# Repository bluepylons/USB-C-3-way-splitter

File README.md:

# A USB-C 3-way-splitter for charging multiple 5W devices from a single USB-PD charger

*Disclaimer* - **Build and/or use this at your own  risk. I am not responsible for anything that arises from use of these files or documents, or for anything that arises from constructing and/or using this device.**

*Disclaimer 2* - the USB battery charging standard actually provides [for a maximum of 1.5A](https://imgur.com/07zPKKw), not 1A as originally believed. The polyfuse used (Littelfuse 1812L300MR) does not reliably trip below 5A, so this splitter may result in 4.5A maximum being drawn from the source. A planned Version 4 (which uses an 3A electronic fuse in place of the high-side switch to reliabily cut off current at around 3A) is being developed to address this issue. UPDATE August 19, 2024 - Version 4 does not work as the ENABLE pin logic for the electronic fuse was inverted. Version 5 is planned to fix this. 

This is a USB-C splitter that splits a 5V 3A-capable USB-C power source to 3 5V 1A  sources. This is for using a single-port USB-C PD charger to charge multiple 5V USB-C devices at once. Files are done in KiCAD 8, and manufacturing files for JLCPCB are provided. An enclosure design is included (which was designed in Autodesk Fusion 360) - .3mf, .step, and .f3z file are provided. 

This design has been prototyped and  tested. 

## Background
With the widespread adoption of USB-C for device charging, I can now travel with a single compact 45W USB-C GaN charger and cable, and charge all my USB-C devices (phone, laptop, camera, flashlight, power bank, headphones, etc.) with that one charger. However, having a single cable and single charger is often limiting when I need to charge multiple devices, especially overnight, and many USB-C devices only need 5V and not many watts for overnight charging. This splitter goes onto an existing USB-C cable, for charging those devices simultaneously with a single charger, without needing a bulkier multi-port charger and multiple cables. 

## Operation 
For safety, the splitter outputs only power on when the splitter is connected to a charger that indicates it can actually supply 3A, and includes a resettable fuse for overcurrent protection. The white LED lights up when it is connected to a powered USB-C cable. The green LED lights up if the power source is capable of supplying 5V 3A, and indicates the outputs have been powered on.

The outputs have D+ and D- shorted to indicate that they can supply ~~~1A~~~ 1.5A of current (per the USB Battery Charging standard). 

## Design
The splitter only powers on with USB-C inputs capable of supplying 5V 3A. This is done by monitoring the USB-C CC lines and checking that the signal there is greater than 1.25V. Under the USB-PD standard, if the voltage on the CC pin [is greater than 1.31V](https://hackaday.com/2023/01/04/all-about-usb-c-resistors-and-emarkers/), it indicates the source is capable of supplying 5V 3A. Only then are the outputs powered on (as indicated by the green LED). Otherwise, the outputs are turned off. 

The CC line voltage checking is done by a pair of comparators that monitor each of the 2 CC lines (as the USB-C input cable can be plugged in either way). The CC line voltage are compared against a 1.25V reference voltage (provided by an ST TS4061AICT-1.25 shunt diode reference) - a 1.31V voltage reference would have been more precise, but were not easily available, and 1.25V is above the 1.16V cutoff for a 1.5A source and works fine. The output of the comparators are fed through a pair of diodes (functioning as an OR gate) to the ENABLE input on an SiP32509 high-side switch that turns the outputs on and off. The device is over-current protected by a 3A resettable fuse (Littelfuse 1812L300MR). The CC lines and +5V bus are ESD protected with an SRV05-4 ESD diode array and an ESD5Z5V0 TVS diode.

Note that the output cables need 56K pull-up resistors between output CC and 5V to comply with the USB-C protocol - some devices may not charge if these resistors are missing. USB-A to USB-C cables are required to include this resistor, so using the USB-C end from a cut-up USB-A to C cable is recommended for the output cables. 

A 3D-printed enclosure design is supplied in the Enclosure folder. The enclosure design is meant to be 3D-printed in two halves; on mine these were printed with translucent PETG to allow the indicator LEDs to shine through. The lower enclosure features embedded M3 nuts - **the print must be paused at the appropriate layer and M3 nuts need to be inserted before the print resumes**. The two halves are screwed together with M3x8 countersunk screws. The enclosure is designed to use [Ikea  SITTBRUNN](https://www.ikea.com/us/en/p/sittbrunn-usb-a-to-usb-c-light-yellow-80539483/) USB-A to USB-C cables, as these are widely available and inexpensive. The ends are wrapped in Qualtek Q5-3X-3/16-01-QB48IN-25 adhesive heatshrink for strain relief. To dissipate heat from the SiP32509 high-side switch (U2), which is expected to generate about 0.4W of heat at 3A, either the enclosure must be potted to facilitate heat transfer, or a thermal pad must be used between the SiP32509 and the case. [Lower-enclosure-potted](https://github.com/bluepylons/USB-C-3-way-splitter/blob/main/Enclosure/Lower-enclosure-potted.3mf) has a small hole to inject potting compound (or hot glue, or silicone) into the case - use a high viscosity potting compound to avoid it getting in the input USB-C connector. [Lower-enclosure-thermal-pad](https://github.com/bluepylons/USB-C-3-way-splitter/blob/main/Enclosure/Lower-enclosure-thermal-pad.3mf) has a small raised feature above the SiP32509 IC to place a 1.5mm thick thermal pad between it and the case. 

# ORDERING GUIDE

## Bill Of Materials

### Custom Parts
| Description                                                                                                                                                                                                                                           | Quantity  | Notes | 
| ----------------------------------------------------------------------------------------------------------------------------------------------------------------------------------------------------------------------------------------------------- | --------- | - |
| [PCB](https://github.com/bluepylons/USB-C-3-way-splitter/tree/main/Manufacturing%20files)                                                                                                                                                             | 1         | See "Ordering the PCB" section below  | 
| [Upper enclosure](https://github.com/bluepylons/USB-C-3-way-splitter/blob/main/Enclosure/Upper-enclosure.3mf)                                                                                                                                         | 1         | FDM 3D-printed  |
| Lower enclosure ([thermal pad](https://github.com/bluepylons/USB-C-3-way-splitter/blob/main/Enclosure/Lower-enclosure-thermal-pad.3mf) or [potted](https://github.com/bluepylons/USB-C-3-way-splitter/blob/main/Enclosure/Lower-enclosure-potted.3mf)) | 1         | FDM 3D-printed. Has 4 embedded M3 nuts, which must be installed while 3D printing | 

The 3D-printed parts were FDM 3D-printed in PETG, though other materials probably work fine here. A translucent or semi-translucent material is recommended so that the indicator LEDs can shine through. 

## Off-the-shelf parts

| Description                                                                                                         | Part number                              | Quantity | Notes                                         | 
| ------------------------------------------------------------------------------------------------------------------- | ---------------------------------------- | -------- | --------------------------------------------- |
| [Ikea Sittbrunn USB-A to USB-C cable](https://www.ikea.com/us/en/p/sittbrunn-usb-a-to-usb-c-light-yellow-80539483/) | Ikea 805.394.83                          | 3        |                                               | 
| M3 hex nut, DIN 934, zinc-plated steel                                                                              | McMaster-Carr 90591A250                  | 4        | Generic. Not stainless steel to avoid galling |
| M3x8 flat head screw, DIN 7991 / ISO 10642, hex drive, 18-8 stainless steel                                         | McMaster-Carr 92125A128                  | 4        | Generic                                       |
| Adhesive-lined heat-shrink, 3/16" / 4.8mm ID, 3:1 shrink ratio                                                      | Qualtek Qualtek Q5-3X-3/16-01-QB48IN-25  | 3x 25mm  |                                               |

If you are using the [thermal pad option](https://github.com/bluepylons/USB-C-3-way-splitter/blob/main/Enclosure/Lower-enclosure-thermal-pad.3mf) for the lower enclosure, you will need 1.5mm thick thermal pads. I used Thermalright Extreme Odyssey 1.5mm pads for the ones I have built, but other 1.5mm thermal pads (e.g. Arctic TP-3) may work. The thermal pad must not be electrically conductive. 

If you are using the [potted option](https://github.com/bluepylons/USB-C-3-way-splitter/blob/main/Enclosure/Lower-enclosure-potted.3mf) for the lower enclosure, you will need some sort of potting compound that can be injected through a 5mm diameter hole. The ones I built used hot glue. Make sure the potting compound has high enough viscosity to not get into the input USB-C port. 

## Ordering the PCB

The PCB can be ordered from [JLCPCB](https://jlcpcb.com/) in China, and the files are provided in their format. 

1.)  Go to JLCPCB, and press "Order Now". 

2.) Next, you want to upload the [Gerber ZIP file](https://github.com/bluepylons/USB-C-3-way-splitter/blob/main/PCB%20manufacturing%20files/V3%20Gerbers.zip) for the PCB. 

3.) Specify the following options once the Gerber file has uploaded. Non-default settings are highlighted in red. 

For color, specify a color supported by JLCPCB's ["Economic PCB Assembly"](https://jlcpcb.com/capabilities/pcb-assembly-capabilities). As of June 30, 2024, green, black, blue, red, white, and purple are supported. Note that some colors might incur an extra fee.

4.) Under "PCB Assembly", specify the following options:

5.) Press "Next":

6.) Upload the [BOM](https://github.com/bluepylons/USB-C-3-way-splitter/blob/main/PCB%20manufacturing%20files/JLCPCB-BOM.xls) and [CPL](https://github.com/bluepylons/USB-C-3-way-splitter/blob/main/PCB%20manufacturing%20files/JLCPCB-CPL.xls) files:

7.) Confirm  the components in the next page. If any components are listed as "Shortfall", JLCPCB does not have enough of them in stock and will not install them on any PCBs. You will have to purchase them from and solder them on yourself. Alternatively, you can wait for JLCPCB to restock the part.

8.) Next is the component placement confirmation page. You should not have to change anything here:

9.) You will need to describe the item in the next page for customs purposes. As of June 30th, 2024, I could not find an option most suitable for this, so select "Office Appliances and Accessories > Others" in the options, and type in "USB cable splitter PCB".

# BUILD GUIDE

## Tools needed 
| Tool           | Purpose                                                                                                                                                     |
| -------------- | ----------------------------------------------------------------------------------------------------------------------------------------------------------- | 
| Flush cutters  | Stripping wires, trimming leads                                                                                                                             |
| Soldering iron | Soldering the USB-C output cables to the PCB                                                                                                                |
| Solder         | You need it to solder                                                                                                                                       |
| Flux           | Makes tinning the output cables easier                                                                                                                      |
| Heat gun       | For the heat-shrink strain relief                                                                                                                           |
| Wire strippers | For stripping wire                                                                                                                                          |

If you are using the thermal pad option for the lower case, you will need scissors to cut the thermal pad. If you are using the potted option, you will need potting compound and whatever tools needed to inject into the hole in the case.

## Build process 

1.) Test the PCB by plugging in a 5V 3A-capable USB-C source. When plugged in, both the white and green LEDs should light up. Next, test it with a non-5V 3A capable source (e.g. use a USB-A cable). When plugged in, only the white LED should light up. 

2.) Unplug the PCB. 

3.) Take the Ikea Sittbrunn USB-A to USB-C cable, and cut the USB-C end to about 20-30mm longer than the desired length.

4.) Strip about 20mm off the outer insulation. The method I found works well is to use a pair of flush cutters to "bite' the insulation parallel to the cable, and then cut the resulting pieces off. After stripping, check that the insulation for the individual wires are not damaged. 

5.) Strip about 10mm off the inner insulation for one of the wires.

6.) Wind  the strands tightly with your hands. 

7.) Apply some flux to the stripped wire.

8.) Tin the wire with a little bit of solder. Try to add enough solder here that the strands don't come apart, but not so much that the stranded wires no longer fit in the output footprint through-holes in the PCB. 

9.) Repeat Steps 5 through 8 for the remaining wires. This is best done one wire at a time to prevent the wires from becoming unstranded from bumping into each other. 

10.) Cut some pieces of heat-shrink that are 20-30mm long:

11.) Put the heat shrink through the cable.

12.) Solder the wires to one of the three output footprints, and trim off any excess using the flush cutters.

The following wire colors correspond to the following pins, which are labelled on the underside of the PCB:

| Color | Pin |
| ----- | --- |
| Black | GND |
| Green | D-  |
| White | D+  |
| Red   | +5V |

Check that the strands from each wire are not shorted to each other. However, since D+ and D- are shorted to each other on the PCB per the USB Battery Charging standard, it does not matter if those two specific wires are shorted to each other. 

13.) Repeat steps 3-12 for the remaining outputs. **Remember to slip the heatshrink tubing on before soldering**. Double check that wires are not shorted to each other. 

14.) Plug the PCB into the 5V 3A USB-C source again. Check that the green and the white lights both light up. If not, you may have a short circuit somewhere.

15.) Move the heatshrink tubing down the cables, like so:

17.) Using a heatgun, shrink the heatshrink:

18.) (For the thermal pad variant only) - Cut a piece of thermal pad to about the size and shape of the raised portion marked in red, and place it on there:

19.) Place the PCB and the soldered wires onto the lower enclosure like so:

20.) Place the upper enclosure on, and attach it with the 4 M3x8 flat head screws.

21.) Test the splitter by plugging it into the 5V 3A source again, and using it to charge various devices (e.g. a phone). Make sure each output works. If not, check your soldering. 

22.) (For the potted variant only) - Inject potting compound into the 5mm hole on the lower enclosure, and it let it dry/solidify/cure. 

You are done!

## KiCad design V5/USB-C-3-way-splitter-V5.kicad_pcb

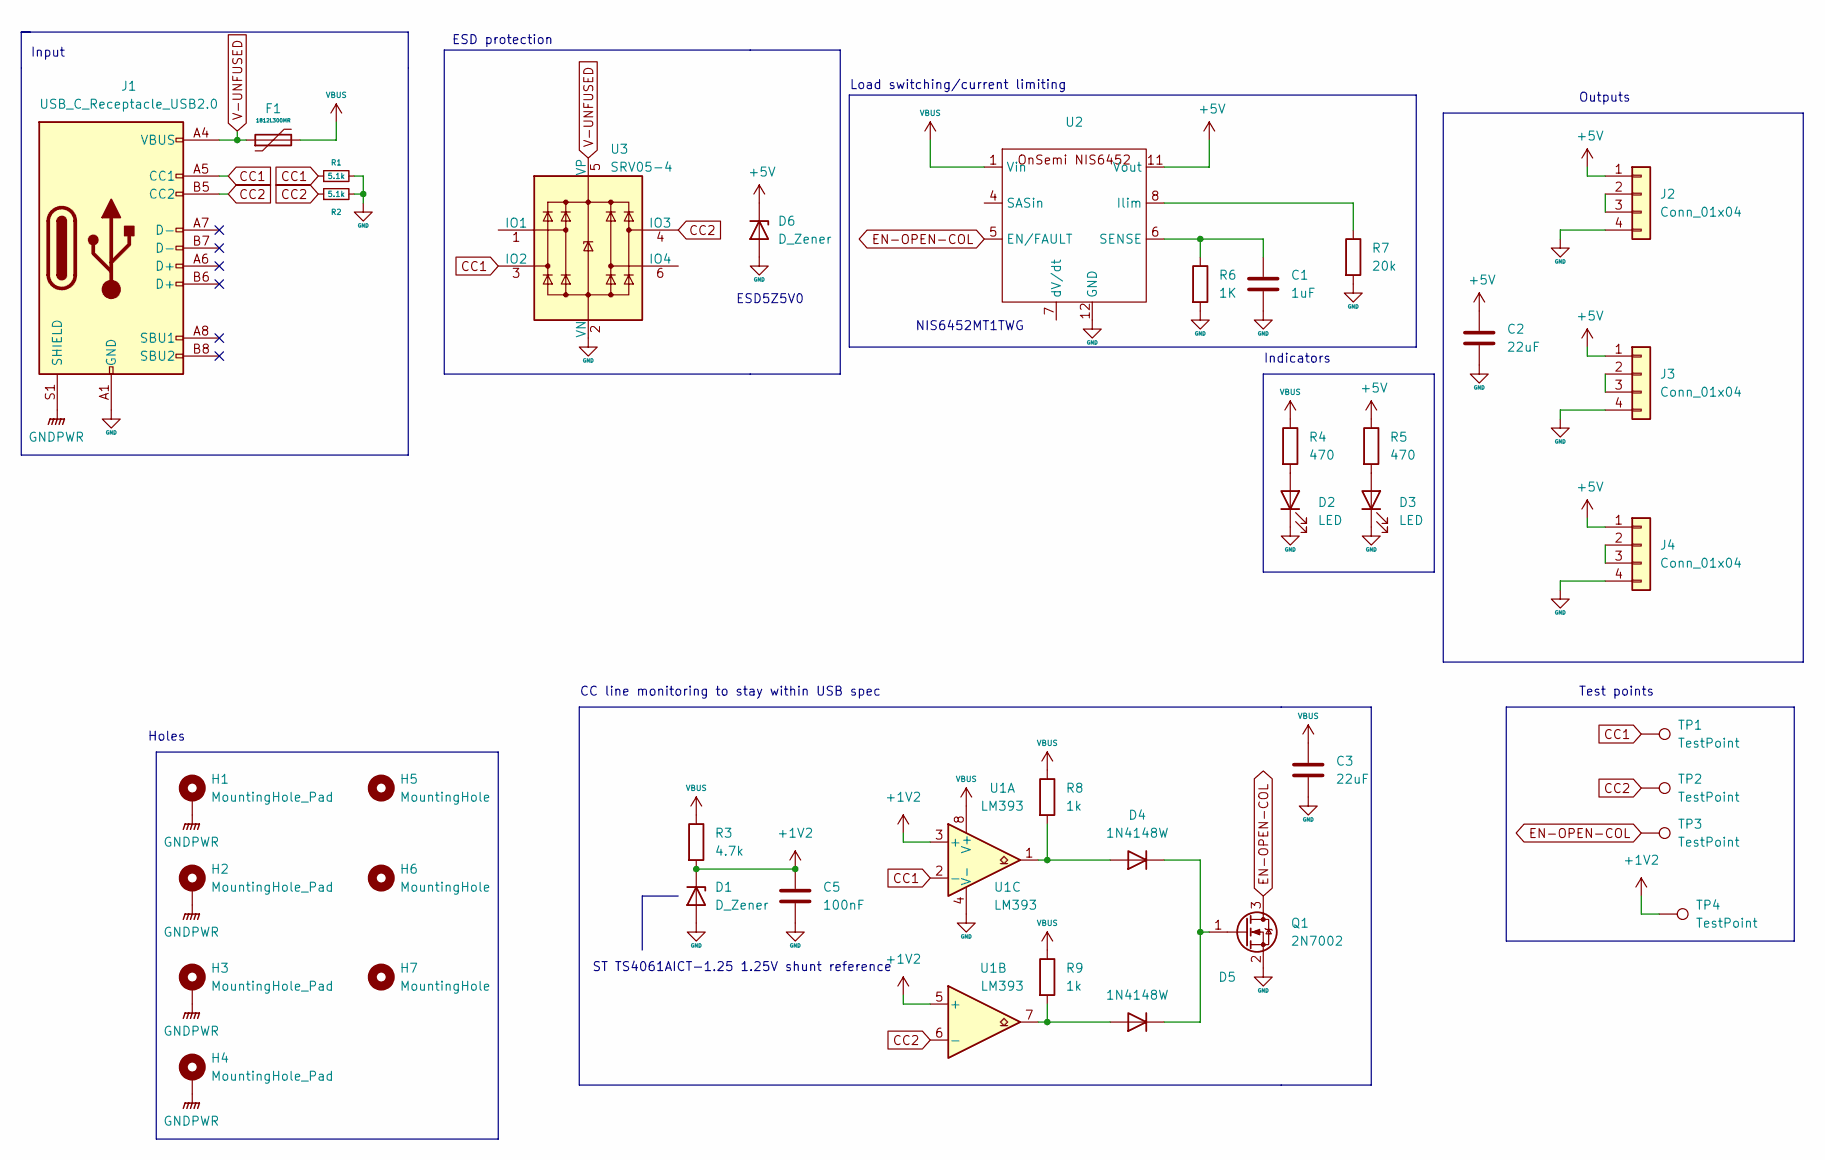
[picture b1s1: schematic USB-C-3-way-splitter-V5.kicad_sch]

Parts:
C1: 1uF; C_0805_2012Metric_Pad1.18x1.45mm_HandSolder
C2, C3: 22uF; C_1206_3216Metric_Pad1.33x1.80mm_HandSolder
C5: 100nF; C_0805_2012Metric_Pad1.18x1.45mm_HandSolder
D1: D_Zener; SOT-323_SC-70_Handsoldering
D2, D3: LED; LED_0805_2012Metric_Pad1.15x1.40mm_HandSolder
D4, D5: 1N4148W; D_SOD-123
D6: D_Zener; D_SOD-523
F1: 1812L300MR; Fuse_1812_4532Metric_Pad1.30x3.40mm_HandSolder; Manufacturer Part No ASMD1206-150; LCSC Part No C135342
H1, H2, H3, H4: MountingHole_Pad; MountingHole_3.2mm_M3_ISO7380_Pad
H5, H6, H7: MountingHole; JLCPCB-tooling-hole
J1: USB_C_Receptacle_USB2.0; USB_C_Receptacle_HRO_TYPE-C-31-M-12; LCSC C165948
J2, J3, J4: Conn_01x04; PinHeader_1x04_P2.00mm_Vertical
Q1: 2N7002; SOT-23
R1, R2: 5.1k; R_0805_2012Metric_Pad1.20x1.40mm_HandSolder
R3: 4.7k; R_0805_2012Metric_Pad1.20x1.40mm_HandSolder
R4, R5: 470; R_0805_2012Metric_Pad1.20x1.40mm_HandSolder
R6: 1K; R_0805_2012Metric_Pad1.20x1.40mm_HandSolder
R7: 20k; R_0805_2012Metric_Pad1.20x1.40mm_HandSolder
R8, R9: 1k; R_0805_2012Metric_Pad1.20x1.40mm_HandSolder
TP1, TP2, TP3, TP4: TestPoint; TestPoint_Pad_D2.5mm
U1: LM393; SOIC-8_3.9x4.9mm_P1.27mm
U2: OnSemi-WQFN12-3x2mm_P0.5mm
U3: SRV05-4; SOT-23-6

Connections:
+1V2: C5.1, D1.1 (K), R3.2, TP4.1, U1.3 (+), U1.5 (+)
+5V: C2.1, D6.1 (K), J2.1, J3.1, J4.1, R5.1, U2.9 (Vout), U2.10 (Vout), U2.11 (Vout)
CC1: J1.A5 (CC1), R1.1, TP1.1, U1.2 (-), U3.3 (IO2)
CC2: J1.B5 (CC2), R2.1, TP2.1, U1.6 (-), U3.4 (IO3)
EN-OPEN-COL: Q1.3 (D), TP3.1, U2.5 (EN/FAULT)
GND: C1.2, C2.2, C3.2, C5.2, D1.2 (A), D2.1 (K), D3.1 (K), D6.2 (A), J1.A1 (GND), J1.A12 (GND), J1.B1 (GND), J1.B12 (GND), J2.4, J3.4, J4.4, Q1.2 (S), R1.2, R2.2, R6.2, R7.2, U1.4 (V-), U2.12 (GND), U2.13 (GND), U3.2 (VN)
GNDPWR: H1.1, H2.1, H3.1, H4.1, J1.S1 (SHIELD)
unnamed: D2.2 (A), R4.2
unnamed: D3.2 (A), R5.2
unnamed: D4.2 (A), R8.2, U1.1
unnamed: D4.1 (K), D5.1 (K), Q1.1 (G)
unnamed: D5.2 (A), R9.2, U1.7
unnamed: J2.2, J2.3
unnamed: J3.2, J3.3
unnamed: J4.2, J4.3
unnamed: R7.1, U2.8 (Ilim)
unnamed: C1.1, R6.1, U2.6 (SENSE)
V-UNFUSED: F1.1, J1.A4 (VBUS), J1.A9 (VBUS), J1.B4 (VBUS), J1.B9 (VBUS), U3.5 (VP)
VBUS: C3.1, F1.2, R3.1, R4.1, R8.1, R9.1, U1.8 (V+), U2.1 (Vin), U2.2 (Vin), U2.3 (Vin)

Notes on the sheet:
ESD protection
ST TS4061AICT-1.25 1.25V shunt reference
Input
NIS6452MT1TWG
CC line monitoring to stay within USB spec
Indicators
ESD5Z5V0
Outputs
Load switching/current limiting
Test points
Holes

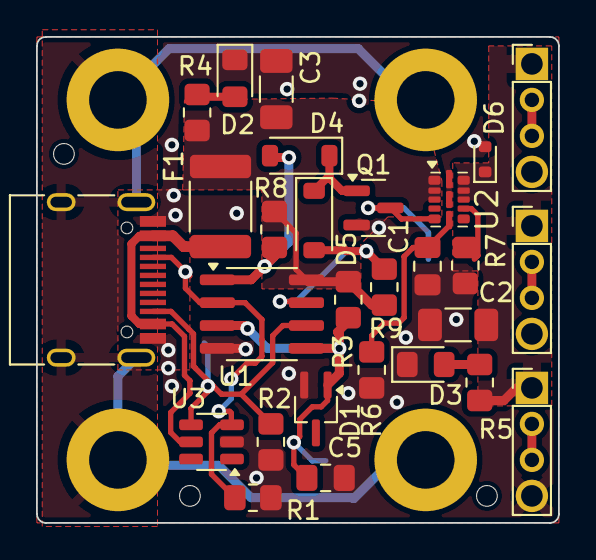
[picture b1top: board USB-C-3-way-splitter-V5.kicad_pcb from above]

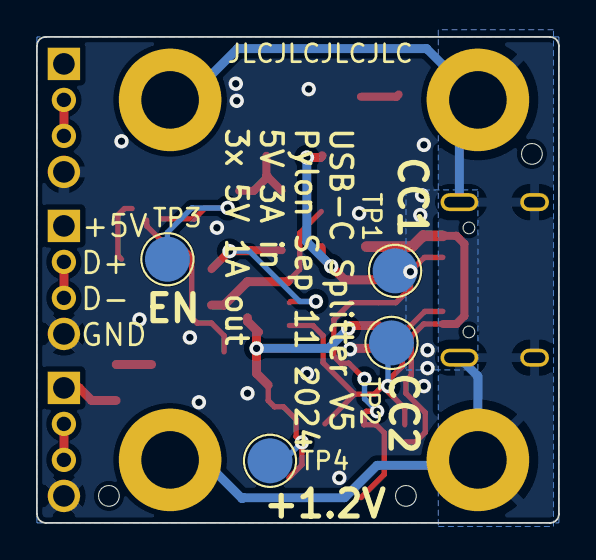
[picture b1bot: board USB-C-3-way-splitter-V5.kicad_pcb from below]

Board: 2 copper layers, 29.0 x 27.0 mm, 39 parts (4 on the bottom side), 19 nets.

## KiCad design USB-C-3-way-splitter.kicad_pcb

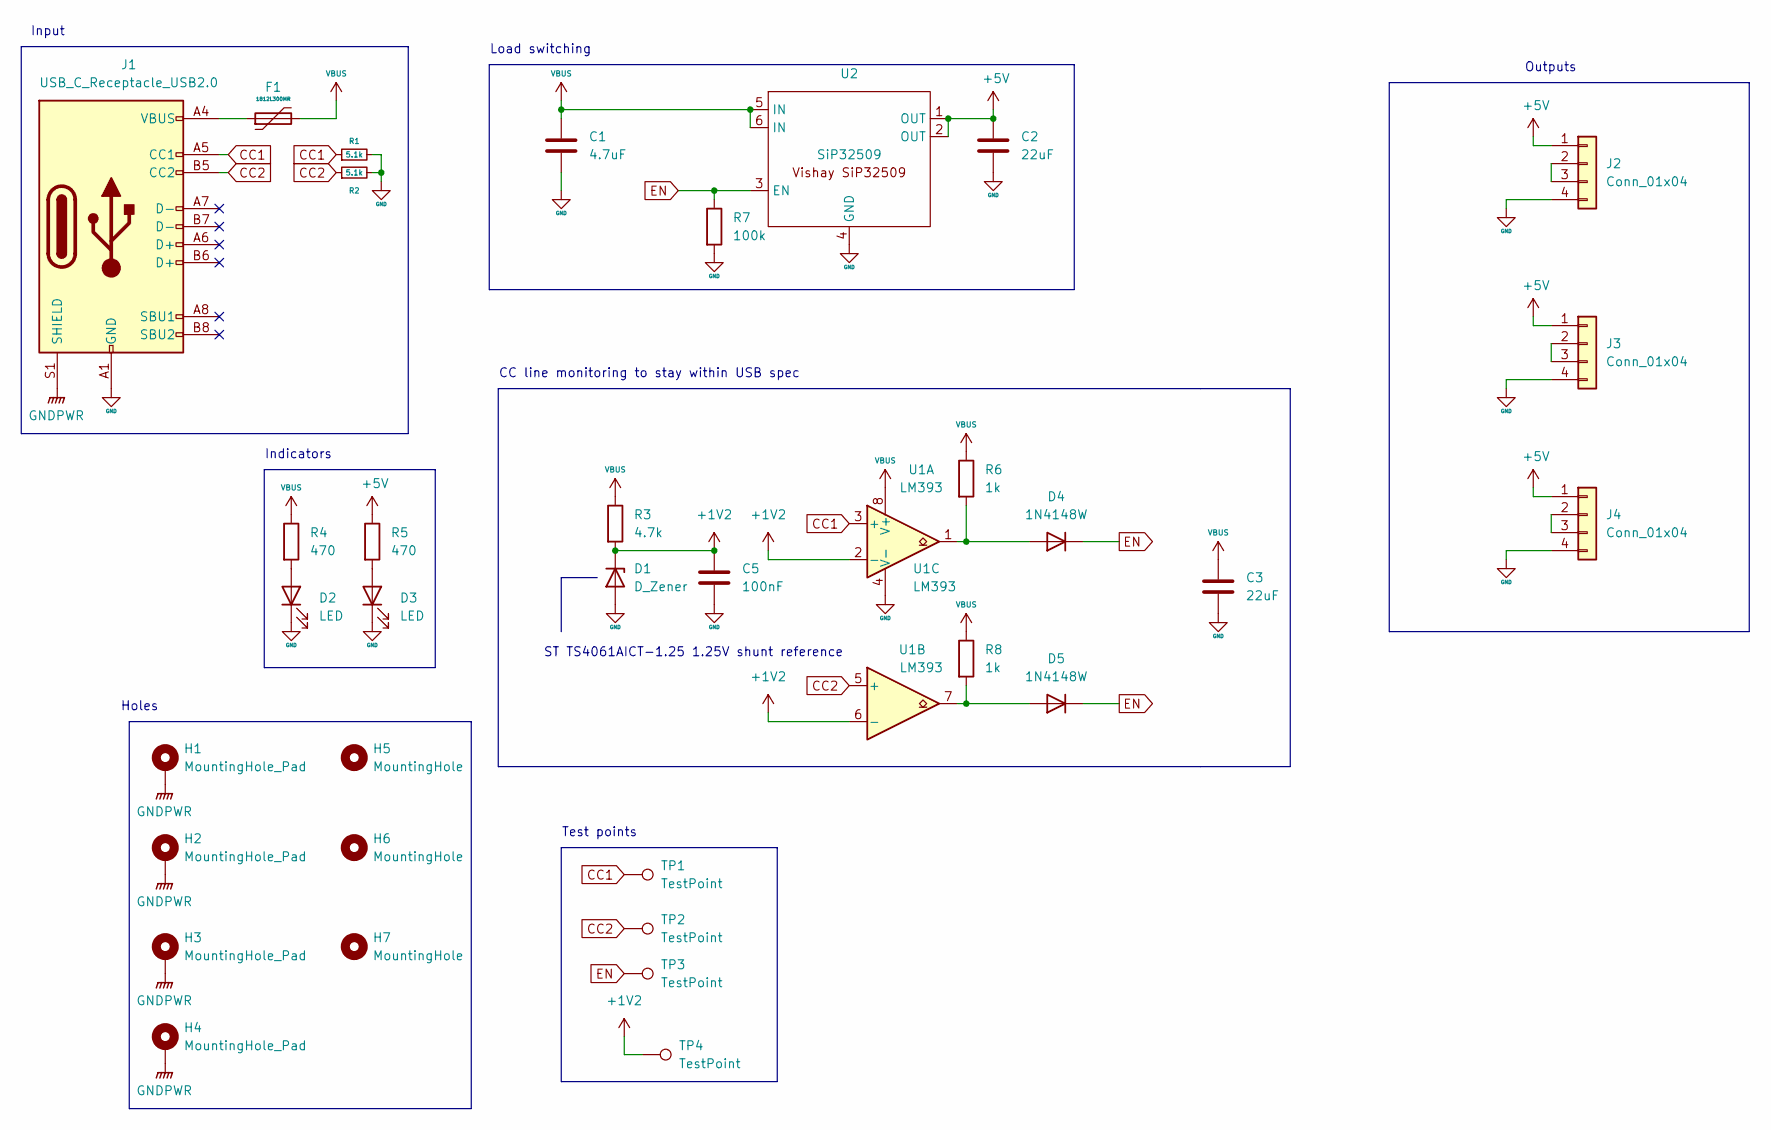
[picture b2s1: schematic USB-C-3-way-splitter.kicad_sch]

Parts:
C1: 4.7uF; C_0805_2012Metric_Pad1.18x1.45mm_HandSolder
C2, C3: 22uF; C_1206_3216Metric_Pad1.33x1.80mm_HandSolder
C5: 100nF; C_0805_2012Metric_Pad1.18x1.45mm_HandSolder
D1: D_Zener; SOT-323_SC-70_Handsoldering
D2, D3: LED; LED_0805_2012Metric_Pad1.15x1.40mm_HandSolder
D4, D5: 1N4148W; D_SOD-123
F1: 1812L300MR; Fuse_1812_4532Metric_Pad1.30x3.40mm_HandSolder; Manufacturer Part No ASMD1206-150; LCSC Part No C135342
H1, H2, H3, H4: MountingHole_Pad; MountingHole_3.2mm_M3_ISO7380_Pad
H5, H6, H7: MountingHole; JLCPCB-tooling-hole
J1: USB_C_Receptacle_USB2.0; USB_C_Receptacle_HRO_TYPE-C-31-M-12; LCSC C165948
J2, J3, J4: Conn_01x04; PinHeader_1x04_P2.00mm_Vertical
R1, R2: 5.1k; R_0805_2012Metric_Pad1.20x1.40mm_HandSolder
R3: 4.7k; R_0805_2012Metric_Pad1.20x1.40mm_HandSolder
R4, R5: 470; R_0805_2012Metric_Pad1.20x1.40mm_HandSolder
R6, R8: 1k; R_0805_2012Metric_Pad1.20x1.40mm_HandSolder
R7: 100k; R_0805_2012Metric_Pad1.20x1.40mm_HandSolder
TP1, TP2, TP3, TP4: TestPoint; TestPoint_Pad_D2.5mm
U1: LM393; SOIC-8_3.9x4.9mm_P1.27mm
U2: SiP32509; TSOT-23-6_HandSoldering

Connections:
+1V2: C5.1, D1.1 (K), R3.2, TP4.1, U1.2 (-), U1.6 (-)
+5V: C2.1, J2.1, J3.1, J4.1, R5.1, U2.1 (OUT), U2.2 (OUT)
CC1: J1.A5 (CC1), R1.1, TP1.1, U1.3 (+)
CC2: J1.B5 (CC2), R2.1, TP2.1, U1.5 (+)
EN: D4.1 (K), D5.1 (K), R7.1, TP3.1, U2.3 (EN)
GND: C1.2, C2.2, C3.2, C5.2, D1.2 (A), D2.1 (K), D3.1 (K), J1.A1 (GND), J1.A12 (GND), J1.B1 (GND), J1.B12 (GND), J2.4, J3.4, J4.4, R1.2, R2.2, R7.2, U1.4 (V-), U2.4 (GND)
GNDPWR: H1.1, H2.1, H3.1, H4.1, J1.S1 (SHIELD)
unnamed: D2.2 (A), R4.2
unnamed: D3.2 (A), R5.2
unnamed: D4.2 (A), R6.2, U1.1
unnamed: D5.2 (A), R8.2, U1.7
unnamed: F1.1, J1.A4 (VBUS), J1.A9 (VBUS), J1.B4 (VBUS), J1.B9 (VBUS)
unnamed: J2.2, J2.3
unnamed: J3.2, J3.3
unnamed: J4.2, J4.3
VBUS: C1.1, C3.1, F1.2, R3.1, R4.1, R6.1, R8.1, U1.8 (V+), U2.5 (IN), U2.6 (IN)

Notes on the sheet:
ST TS4061AICT-1.25 1.25V shunt reference
Input
CC line monitoring to stay within USB spec
Indicators
Outputs
Load switching
Test points
Holes

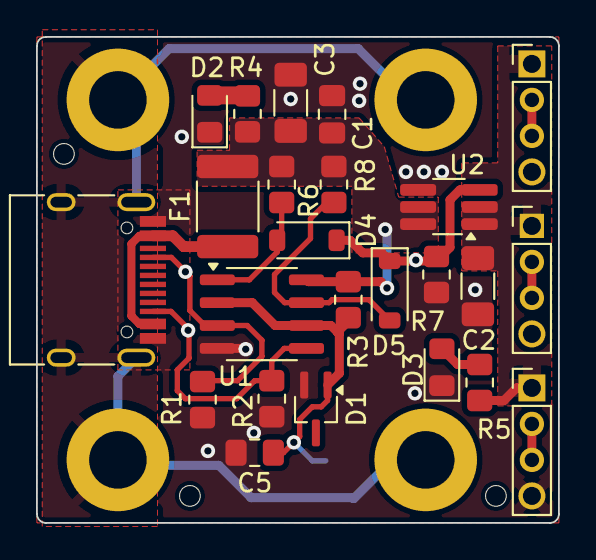
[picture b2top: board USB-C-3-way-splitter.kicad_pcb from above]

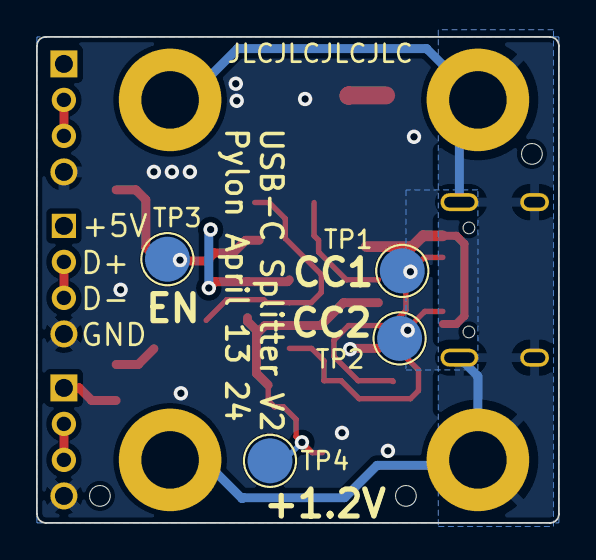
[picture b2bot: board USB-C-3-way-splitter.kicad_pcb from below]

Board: 2 copper layers, 29.0 x 27.0 mm, 35 parts (4 on the bottom side), 16 nets.

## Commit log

2024-02-14 Removed backup files
2024-02-14 Moved everything on the 5v rail to after the fuse
2024-02-14 Made Gerbers
2024-02-14 Open-collectors are inverting ugh. Fixed comparator in schematic.
2024-02-14 Layout is incorrect (had to fix schematic)
2024-02-14 Never mind misunderstood the LM393M's behavior
2024-02-15 Design is done maybe?
2024-02-15 Added JLCPCB tooling holes
2024-02-15 Added schematic
2024-02-15 Added pulldown to EN, added test points
2024-02-15 Removed unnecessary diodes and resistor
2024-03-10 Added enclosure design
2024-03-10 Reorg, status update, added case
2024-03-11 Design updates
2024-04-13 Redesigned to fix circuit design error
    The previous revision had the comparator outputs implemented as an AND instead of an OR, which was preventing the switch from ever turning on.
2024-04-13 Added label
2024-04-13 Minor silkscreen revisions
2024-04-13 Updated design files for V2
2024-04-14 Added STEP file of the PCB
2024-04-18 Rev 2 after Rev 1 did not work
2024-05-04 Updated files
2024-05-04 Added note on JLCPCB
2024-05-05 Fixed board thickness
2024-05-16 Added V3, updated README
2024-05-30 Added graphics
2024-05-30 Revised enclosure
2024-06-04 Added picture
2024-06-04 Updated project status
2024-06-04 Updated status
2024-06-08 Updated status of ESD protection
2024-06-29 Some organization and updates
2024-06-29 Added build guide images
2024-06-30 A bit of reorganization; adding graphics
2024-06-30 Updated graphics
2024-06-30 More graphics
2024-06-30 Reorganization
2024-06-30 (WIP) worked on ordering and build guide
2024-06-30 Updated the STEP file
2024-06-30 Bolded some text
2024-06-30 Updated README again
2024-06-30 More work on the README.md
2024-06-30 Flipped 180° to match the prior pic
2024-07-01 Updated some of the wording
2024-07-01 Fixed a typo
2024-07-01 More wording changes for clarity
2024-07-07 Added issue about USB BC
2024-07-08 Work on V4
2024-07-08 More work on V4
2024-08-20 Updated on Version 4
2024-09-12 Started a V5
2025-04-13 Work on V5
2025-04-13 Fixed rotation on U2
